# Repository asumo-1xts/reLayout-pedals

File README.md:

# reLayout-pedals

非営利な目的のもと、既存のエフェクターの基板レイアウトを引きなおします。

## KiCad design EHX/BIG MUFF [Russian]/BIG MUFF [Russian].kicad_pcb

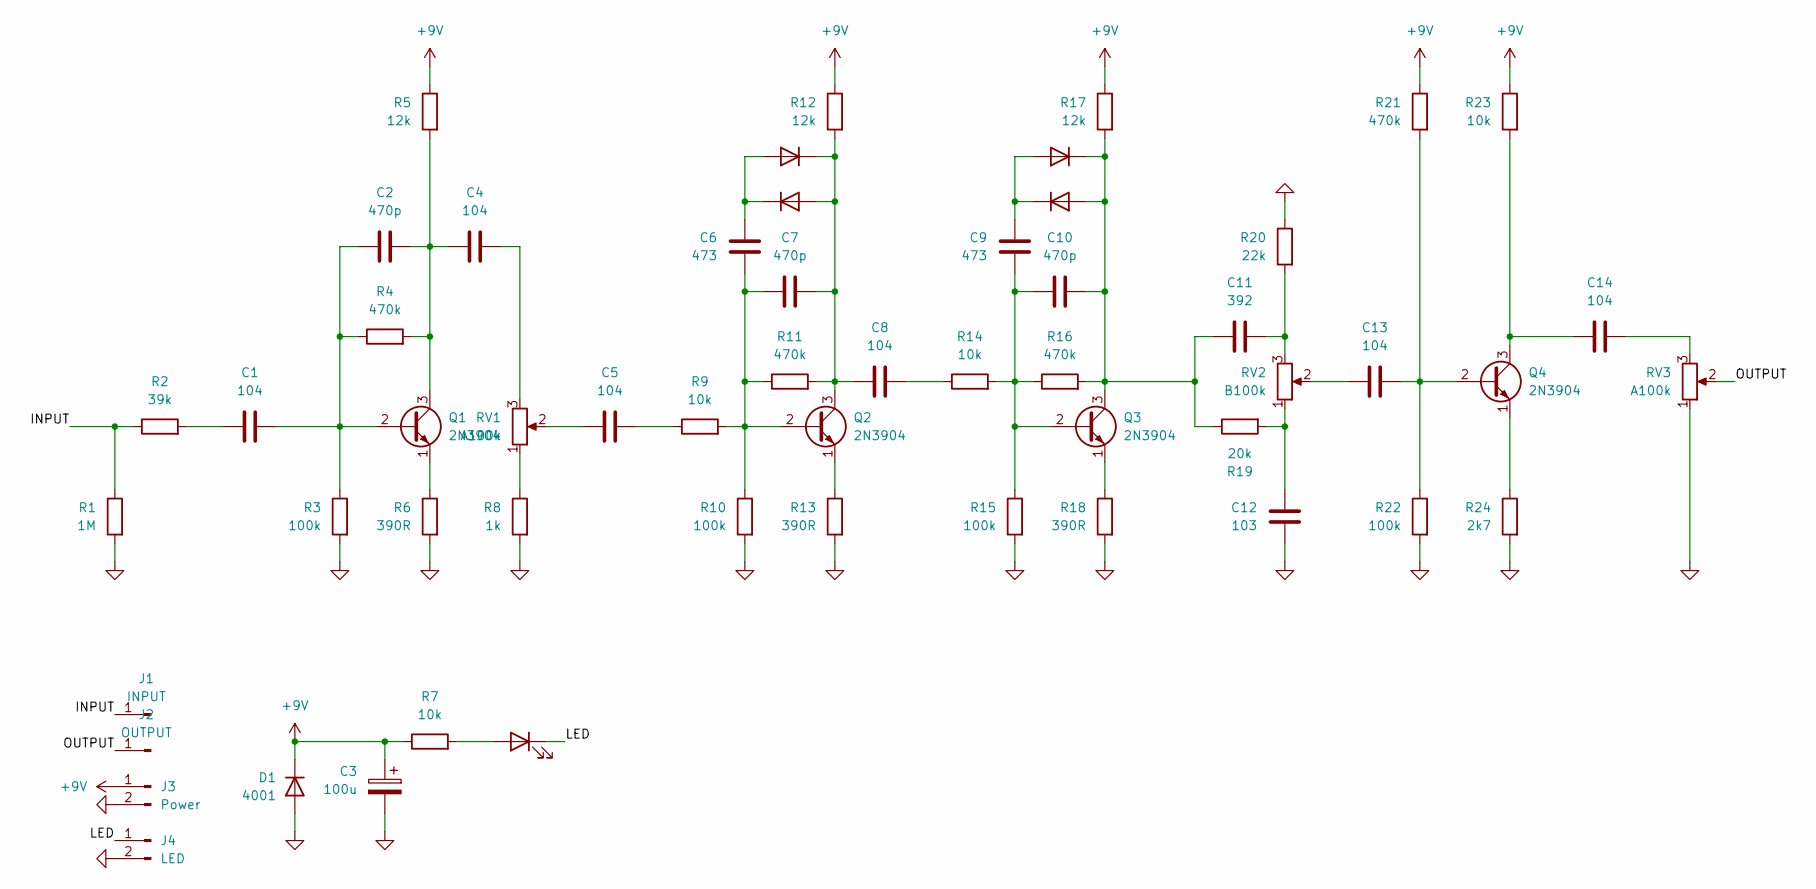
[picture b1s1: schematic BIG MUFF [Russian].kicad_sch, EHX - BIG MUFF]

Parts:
C1, C4, C5, C8, C13, C14: 104; C_Rect_L10.3mm_W5.7mm_P7.50mm_MKS4
C2, C7, C10: 470p; C_Rect_L7.2mm_W3.0mm_P5.00mm_FKS2_FKP2_MKS2_MKP2
C3: 100u; CP_Radial_D8.0mm_P3.50mm
C6, C9: 473; C_Rect_L7.2mm_W3.0mm_P5.00mm_FKS2_FKP2_MKS2_MKP2
C11: 392; C_Rect_L7.2mm_W3.0mm_P5.00mm_FKS2_FKP2_MKS2_MKP2
C12: 103; C_Rect_L7.2mm_W3.0mm_P5.00mm_FKS2_FKP2_MKS2_MKP2
D1: 4001; D_DO-41_SOD81_P7.62mm_Horizontal
D2: LED; LED_D5.0mm
D7, D8, D9, D10: 1N4148; D_DO-35_SOD27_P5.08mm_Vertical_AnodeUp
J1: INPUT; PinHeader_1x01_P2.54mm_Vertical
J2: OUTPUT; PinHeader_1x01_P2.54mm_Vertical
J3: Power; PinHeader_1x02_P2.54mm_Vertical
J4: LED; PinHeader_1x02_P2.54mm_Vertical
Q1, Q2, Q3, Q4: 2N3904; TO-92_Inline_Wide
R1: 1M; R_Axial_DIN0207_L6.3mm_D2.5mm_P7.62mm_Horizontal
R2: 39k; R_Axial_DIN0207_L6.3mm_D2.5mm_P7.62mm_Horizontal
R3, R10, R15, R22: 100k; R_Axial_DIN0207_L6.3mm_D2.5mm_P7.62mm_Horizontal
R4, R11, R16, R21: 470k; R_Axial_DIN0207_L6.3mm_D2.5mm_P7.62mm_Horizontal
R5, R12, R17: 12k; R_Axial_DIN0207_L6.3mm_D2.5mm_P7.62mm_Horizontal
R6, R13, R18: 390R; R_Axial_DIN0207_L6.3mm_D2.5mm_P7.62mm_Horizontal
R7, R9, R14, R23: 10k; R_Axial_DIN0207_L6.3mm_D2.5mm_P7.62mm_Horizontal
R8: 1k; R_Axial_DIN0207_L6.3mm_D2.5mm_P7.62mm_Horizontal
R19: 20k; R_Axial_DIN0207_L6.3mm_D2.5mm_P7.62mm_Horizontal
R20: 22k; R_Axial_DIN0207_L6.3mm_D2.5mm_P7.62mm_Horizontal
R24: 2k7; R_Axial_DIN0207_L6.3mm_D2.5mm_P7.62mm_Horizontal
RV1, RV3: A100k; Potentiometer_Omeg_PC16BU_Vertical
RV2: B100k; Potentiometer_Omeg_PC16BU_Vertical

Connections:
+9V: C3.1, D1.1 (K), J3.1, R5.1, R7.1, R12.1, R17.1, R21.1, R23.1
/INPUT: J1.1 (Pin_1_1), R1.1, R2.1
/LED: D2.1 (K), J4.1
/OUTPUT: J2.1 (Pin_1_1), RV3.2
GND: C3.2, C12.2, D1.2 (A), J3.2, J4.2, R1.2, R3.2, R6.2, R8.2, R10.2, R13.2, R15.2, R18.2, R20.1, R22.2, R24.2, RV3.1
unnamed: C1.1, R2.2
unnamed: C4.2, RV1.3
unnamed: C5.1, RV1.2
unnamed: C5.2, R9.1
unnamed: C8.2, R14.1
unnamed: C11.2, R20.2, RV2.3
unnamed: C12.1, R19.2, RV2.1
unnamed: C13.1, RV2.2
unnamed: C14.2, RV3.3
unnamed: D2.2 (A), R7.2
unnamed: C7.2, C8.1, D7.2 (A), D8.1 (K), Q2.3 (C), R11.2, R12.2
unnamed: C6.1, D7.1 (K), D8.2 (A)
unnamed: C9.1, D9.1 (K), D10.2 (A)
unnamed: C10.2, C11.1, D9.2 (A), D10.1 (K), Q3.3 (C), R16.2, R17.2, R19.1
unnamed: C1.2, C2.1, Q1.2 (B), R3.1, R4.1
unnamed: C2.2, C4.1, Q1.3 (C), R4.2, R5.2
unnamed: Q1.1 (E), R6.1
unnamed: C6.2, C7.1, Q2.2 (B), R9.2, R10.1, R11.1
unnamed: Q2.1 (E), R13.1
unnamed: C9.2, C10.1, Q3.2 (B), R14.2, R15.1, R16.1
unnamed: Q3.1 (E), R18.1
unnamed: C13.2, Q4.2 (B), R21.2, R22.1
unnamed: C14.1, Q4.3 (C), R23.2
unnamed: Q4.1 (E), R24.1
unnamed: R8.1, RV1.1

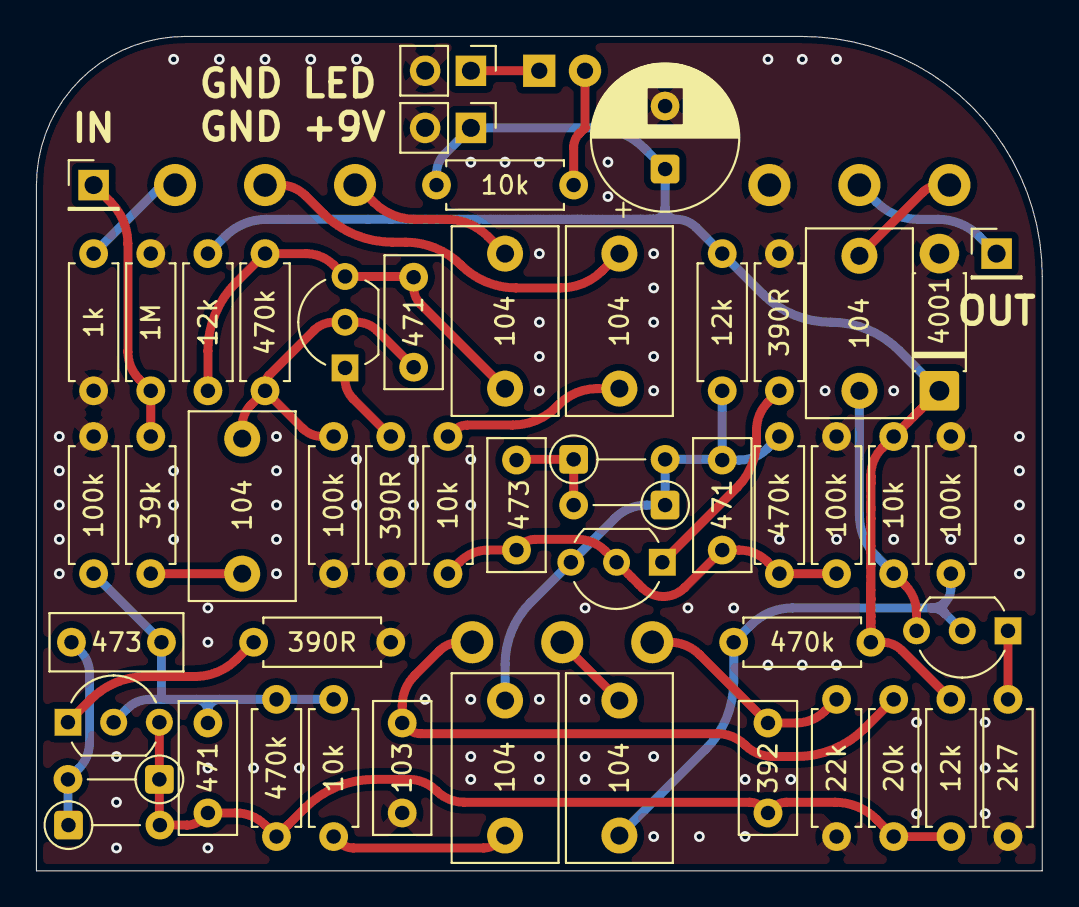
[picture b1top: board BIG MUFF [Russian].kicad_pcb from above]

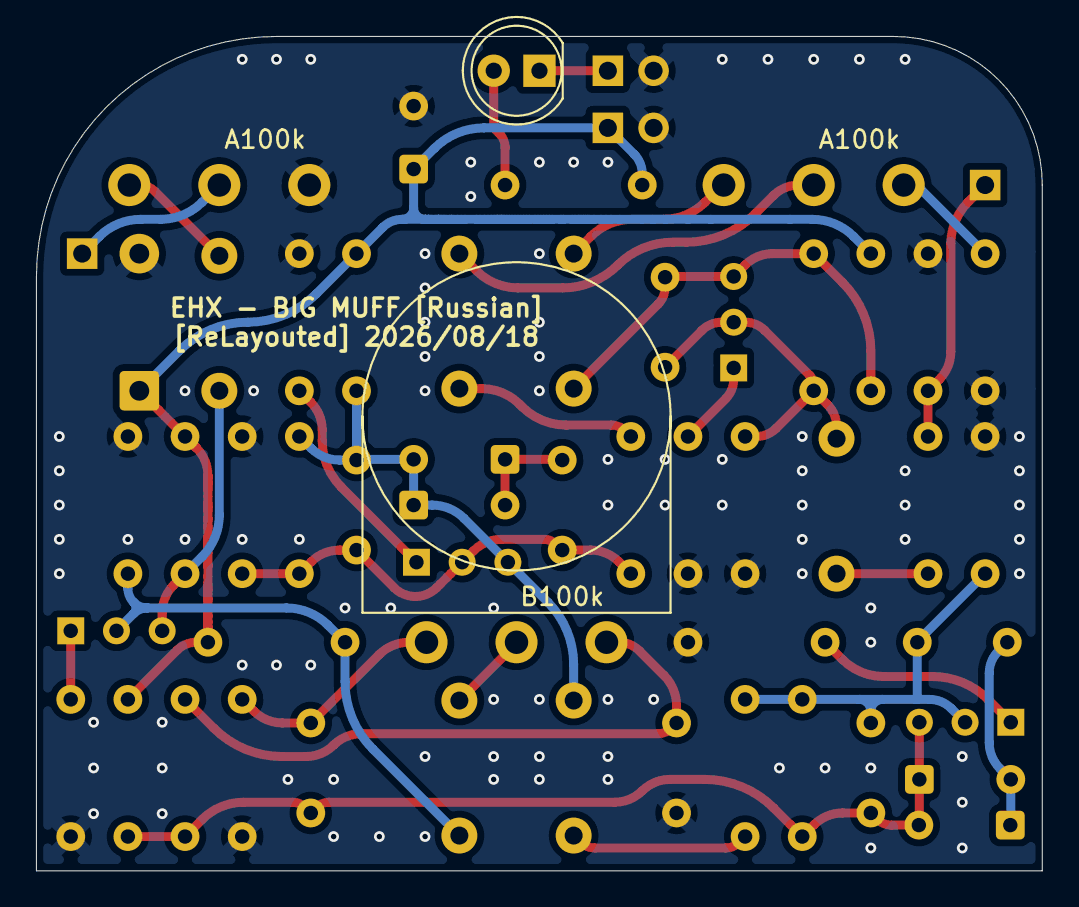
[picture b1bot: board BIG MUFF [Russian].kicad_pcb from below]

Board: 2 copper layers, 55.9 x 46.4 mm, 55 parts (4 on the bottom side), 30 nets.

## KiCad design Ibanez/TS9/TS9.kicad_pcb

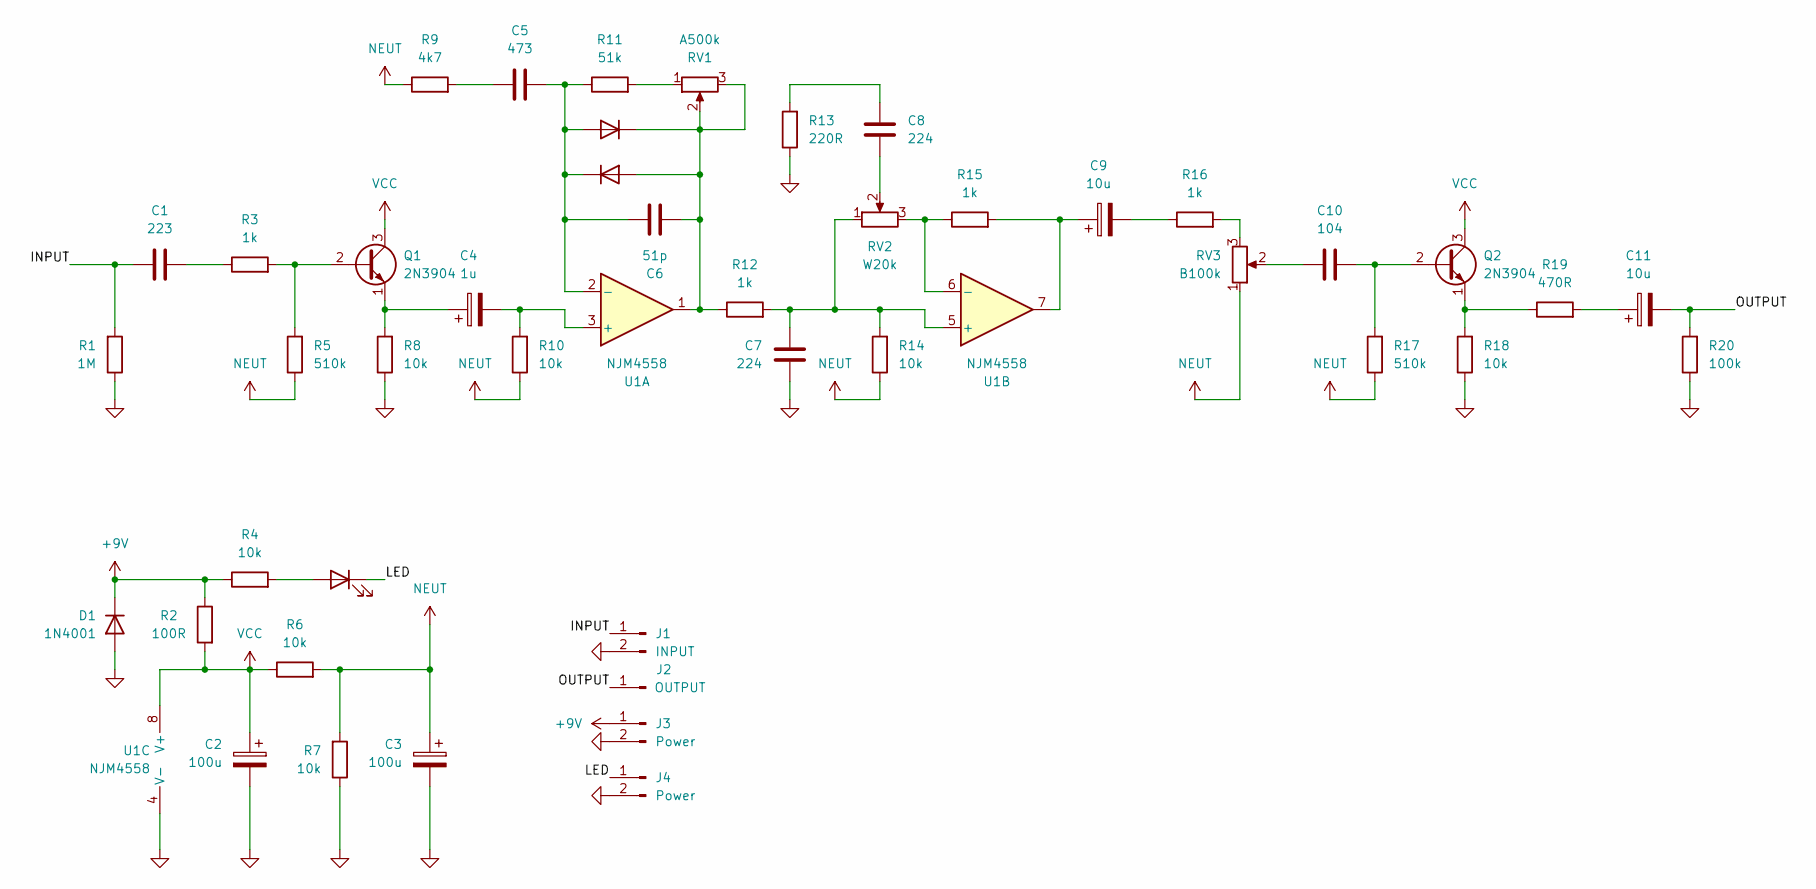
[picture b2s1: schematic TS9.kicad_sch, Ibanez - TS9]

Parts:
C1: 223; C_Rect_L7.2mm_W3.0mm_P5.00mm_FKS2_FKP2_MKS2_MKP2
C2, C3: 100u; CP_Radial_D8.0mm_P3.50mm
C4: 1u; CP_Radial_D5.0mm_P2.00mm
C5: 473; C_Rect_L7.2mm_W3.0mm_P5.00mm_FKS2_FKP2_MKS2_MKP2
C6: 51p; C_Disc_D3.8mm_W2.6mm_P2.50mm
C7, C8: 224; C_Rect_L10.3mm_W5.7mm_P7.50mm_MKS4
C9, C11: 10u; CP_Radial_D5.0mm_P2.00mm
C10: 104; C_Rect_L10.3mm_W5.7mm_P7.50mm_MKS4
D1: 1N4001; D_DO-41_SOD81_P7.62mm_Horizontal
D2: LED; LED_D5.0mm
D3, D4: 1N4148; D_DO-35_SOD27_P5.08mm_Vertical_AnodeUp
J1: INPUT; PinHeader_1x02_P2.54mm_Vertical
J2: OUTPUT; PinHeader_1x01_P2.54mm_Vertical
J3, J4: Power; PinHeader_1x02_P2.54mm_Vertical
Q1, Q2: 2N3904; TO-92_Inline_Wide
R1: 1M; R_Axial_DIN0207_L6.3mm_D2.5mm_P7.62mm_Horizontal
R2: 100R; R_Axial_DIN0207_L6.3mm_D2.5mm_P7.62mm_Horizontal
R3, R12, R15, R16: 1k; R_Axial_DIN0207_L6.3mm_D2.5mm_P7.62mm_Horizontal
R4, R6, R7, R8, R10, R14, R18: 10k; R_Axial_DIN0207_L6.3mm_D2.5mm_P7.62mm_Horizontal
R5, R17: 510k; R_Axial_DIN0207_L6.3mm_D2.5mm_P7.62mm_Horizontal
R9: 4k7; R_Axial_DIN0207_L6.3mm_D2.5mm_P7.62mm_Horizontal
R11: 51k; R_Axial_DIN0207_L6.3mm_D2.5mm_P7.62mm_Horizontal
R13: 220R; R_Axial_DIN0207_L6.3mm_D2.5mm_P7.62mm_Horizontal
R19: 470R; R_Axial_DIN0207_L6.3mm_D2.5mm_P7.62mm_Horizontal
R20: 100k; R_Axial_DIN0207_L6.3mm_D2.5mm_P7.62mm_Horizontal
RV1: A500k; Potentiometer_Omeg_PC16BU_Vertical
RV2: W20k; Potentiometer_Omeg_PC16BU_Vertical
RV3: B100k; Potentiometer_Omeg_PC16BU_Vertical
U1: NJM4558; DIP-8_W7.62mm

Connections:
+9V: D1.1 (K), J3.1, R2.1, R4.1
/INPUT: C1.2, J1.1, R1.2
/LED: D2.1 (K), J4.1
/OUTPUT: C11.2, J2.1 (Pin_1_1), R20.2
GND: C2.2, C3.2, C7.2, D1.2 (A), J1.2, J3.2, J4.2, R1.1, R7.1, R8.1, R13.1, R18.1, R20.1, U1.4 (V-)
NEUT: C3.1, R5.1, R6.2, R7.2, R9.1, R10.1, R14.1, R17.1, RV3.1
unnamed: C1.1, R3.1
unnamed: C5.2, R9.2
unnamed: C8.1, R13.2
unnamed: C8.2, RV2.2
unnamed: C9.1, R15.2, U1.7
unnamed: C9.2, R16.1
unnamed: C10.2, RV3.2
unnamed: C11.1, R19.2
unnamed: D2.2 (A), R4.2
unnamed: C5.1, C6.2, D3.2 (A), D4.1 (K), R11.1, U1.2 (-)
unnamed: C6.1, D3.1 (K), D4.2 (A), R12.1, RV1.2, RV1.3, U1.1
unnamed: Q1.2 (B), R3.2, R5.2
unnamed: C4.1, Q1.1 (E), R8.2
unnamed: C10.1, Q2.2 (B), R17.2
unnamed: Q2.1 (E), R18.2, R19.1
unnamed: R11.2, RV1.1
unnamed: R16.2, RV3.3
unnamed: C4.2, R10.2, U1.3 (+)
unnamed: C7.1, R12.2, R14.2, RV2.1, U1.5 (+)
unnamed: R15.1, RV2.3, U1.6 (-)
VCC: C2.1, Q1.3 (C), Q2.3 (C), R2.2, R6.1, U1.8 (V+)

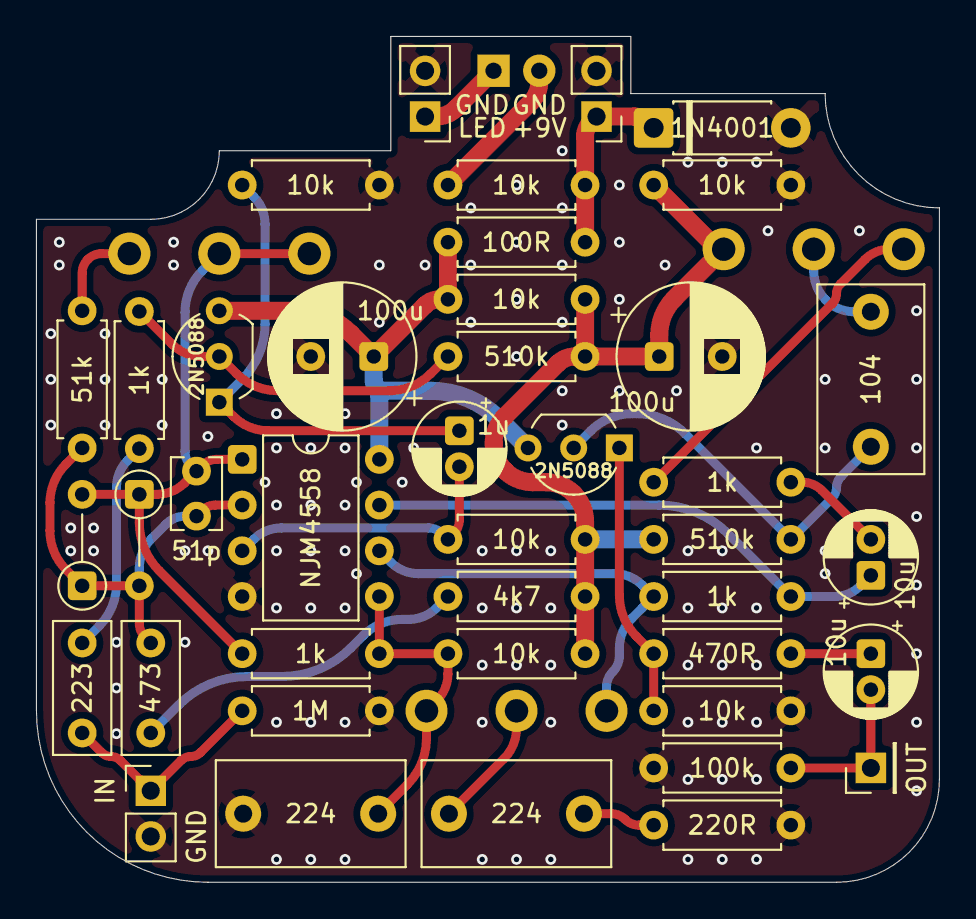
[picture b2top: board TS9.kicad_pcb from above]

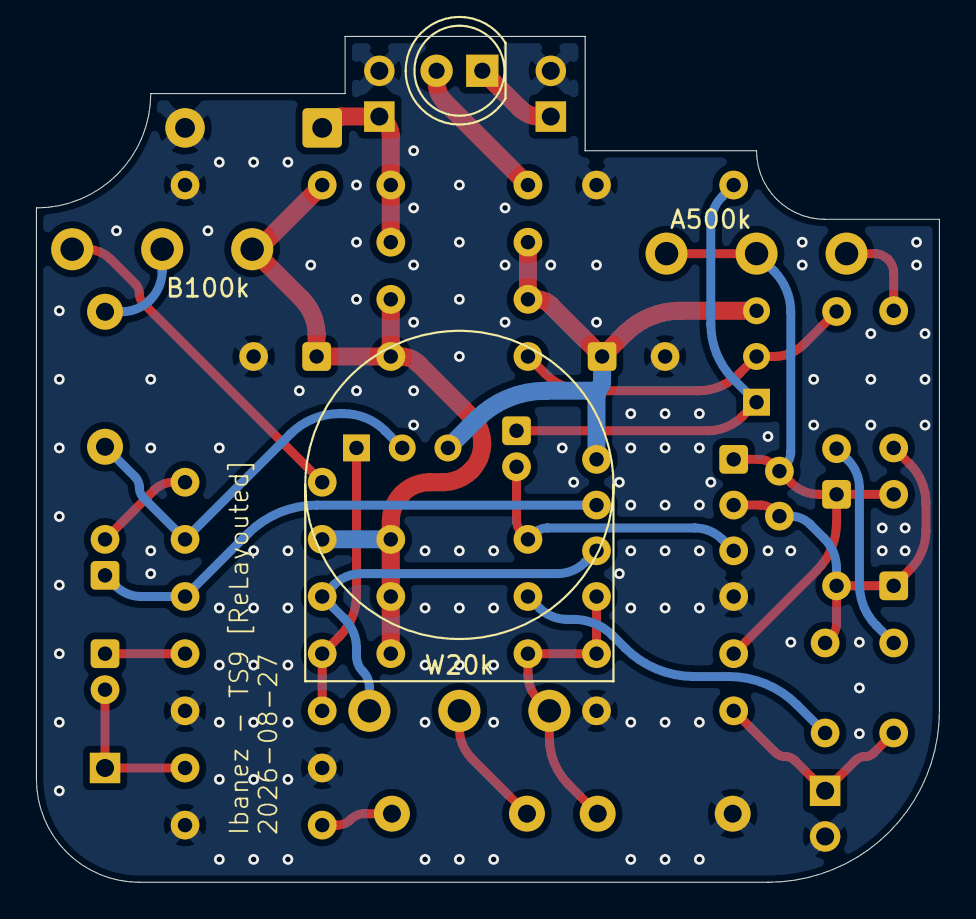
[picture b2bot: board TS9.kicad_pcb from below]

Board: 2 copper layers, 50.2 x 47.0 mm, 45 parts (4 on the bottom side), 27 nets.

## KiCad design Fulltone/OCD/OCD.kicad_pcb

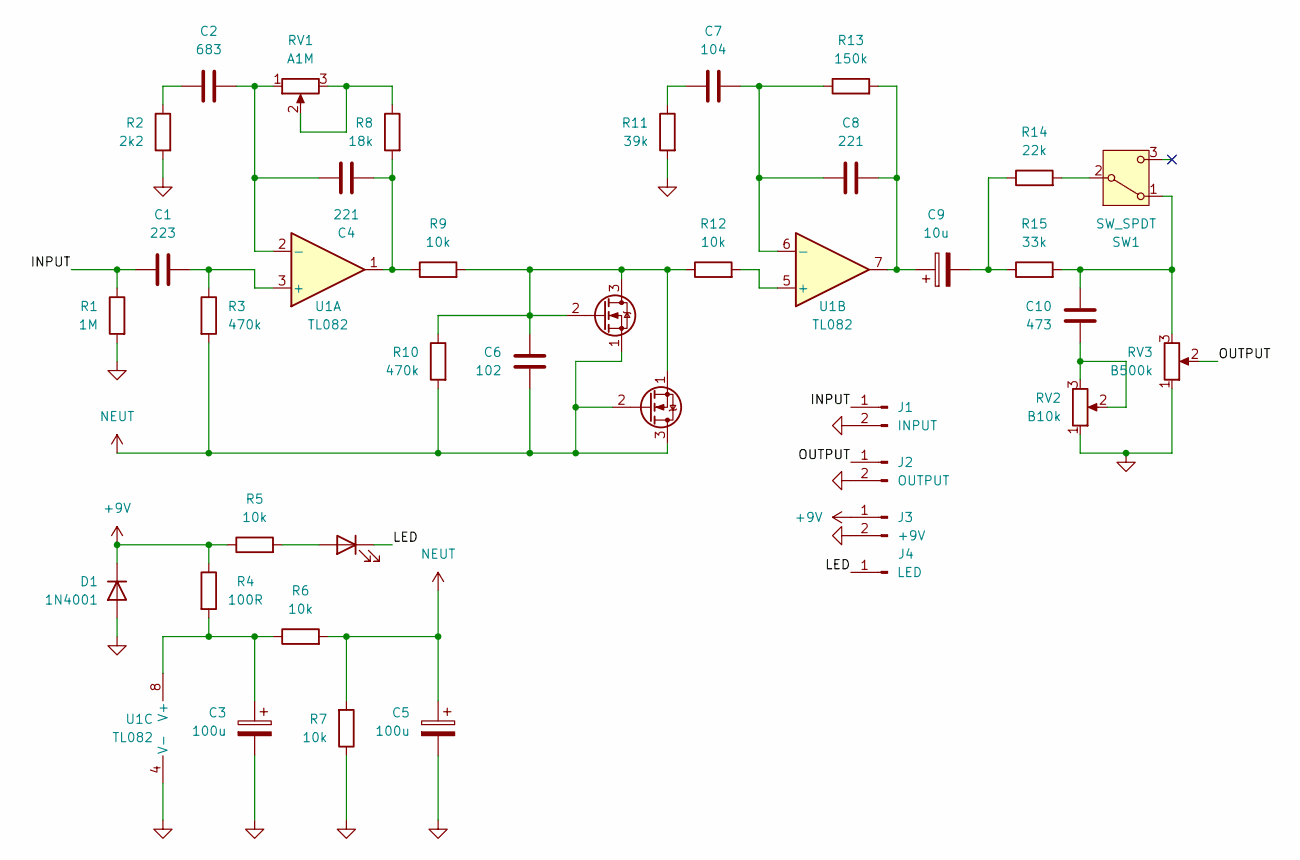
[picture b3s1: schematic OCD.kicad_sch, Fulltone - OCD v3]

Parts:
C1: 223; C_Rect_L7.2mm_W3.0mm_P5.00mm_FKS2_FKP2_MKS2_MKP2
C2: 683; C_Rect_L7.2mm_W4.5mm_P5.00mm_FKS2_FKP2_MKS2_MKP2
C3, C5: 100u; CP_Radial_D8.0mm_P3.50mm
C4, C8: 221; C_Rect_L7.2mm_W3.0mm_P5.00mm_FKS2_FKP2_MKS2_MKP2
C6: 102; C_Rect_L7.2mm_W3.0mm_P5.00mm_FKS2_FKP2_MKS2_MKP2
C7: 104; C_Rect_L10.3mm_W5.7mm_P7.50mm_MKS4
C9: 10u; CP_Radial_D5.0mm_P2.00mm
C10: 473; C_Rect_L7.2mm_W3.0mm_P5.00mm_FKS2_FKP2_MKS2_MKP2
D1: 1N4001; D_DO-41_SOD81_P7.62mm_Horizontal
D2: LED; LED_D5.0mm
J1: INPUT; PinHeader_1x02_P2.54mm_Vertical
J2: OUTPUT; PinHeader_1x02_P2.54mm_Vertical
J3: +9V; PinHeader_1x02_P2.54mm_Vertical
J4: LED; PinHeader_1x01_P2.54mm_Vertical
Q1, Q2: 2N7000; TO-92_Inline_Wide
R1: 1M; R_Axial_DIN0207_L6.3mm_D2.5mm_P7.62mm_Horizontal
R2: 2k2; R_Axial_DIN0207_L6.3mm_D2.5mm_P7.62mm_Horizontal
R3, R10: 470k; R_Axial_DIN0207_L6.3mm_D2.5mm_P7.62mm_Horizontal
R4: 100R; R_Axial_DIN0207_L6.3mm_D2.5mm_P7.62mm_Horizontal
R5, R6, R7, R9, R12: 10k; R_Axial_DIN0207_L6.3mm_D2.5mm_P7.62mm_Horizontal
R8: 18k; R_Axial_DIN0207_L6.3mm_D2.5mm_P7.62mm_Horizontal
R11: 39k; R_Axial_DIN0207_L6.3mm_D2.5mm_P7.62mm_Horizontal
R13: 150k; R_Axial_DIN0207_L6.3mm_D2.5mm_P7.62mm_Horizontal
R14: 22k; R_Axial_DIN0207_L6.3mm_D2.5mm_P7.62mm_Horizontal
R15: 33k; R_Axial_DIN0207_L6.3mm_D2.5mm_P7.62mm_Horizontal
RV1: A1M; Potentiometer_Omeg_PC16BU_Vertical
RV2: B10k; Potentiometer_Omeg_PC16BU_Vertical
RV3: B500k; Potentiometer_Omeg_PC16BU_Vertical
SW1: SW_SPDT; PinHeader_1x03_P2.54mm_Vertical
U1: TL082; DIP-8_W7.62mm

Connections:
+9V: D1.1 (K), J3.1, R4.1, R5.1
/INPUT: C1.1, J1.1, R1.1
/LED: D2.1 (K), J4.1 (Pin_1_1)
/OUTPUT: J2.1, RV3.2
GND: C3.2, C5.2, D1.2 (A), J1.2, J2.2, J3.2, R1.2, R2.2, R7.1, R11.2, RV2.1, RV3.1, U1.4 (V-)
NEUT: C5.1, C6.2, Q1.1 (S), Q2.2 (G), Q2.3 (D), R3.2, R6.2, R7.2, R10.2
unnamed: C2.1, R2.1
unnamed: C4.2, R8.2, R9.1, U1.1
unnamed: C7.1, R11.1
unnamed: C8.2, C9.1, R13.2, U1.7
unnamed: C9.2, R14.1, R15.1
unnamed: C10.2, RV2.2, RV2.3
unnamed: D2.2 (A), R5.2
unnamed: C6.1, Q1.2 (G), Q1.3 (D), Q2.1 (S), R9.2, R10.1, R12.1
unnamed: R8.1, RV1.2, RV1.3
unnamed: C10.1, R15.2, RV3.3, SW1.1 (A)
unnamed: R14.2, SW1.2 (B)
unnamed: C1.2, R3.1, U1.3 (+)
unnamed: C2.2, C4.1, RV1.1, U1.2 (-)
unnamed: R12.2, U1.5 (+)
unnamed: C7.2, C8.1, R13.1, U1.6 (-)
unnamed: C3.1, R4.2, R6.1, U1.8 (V+)

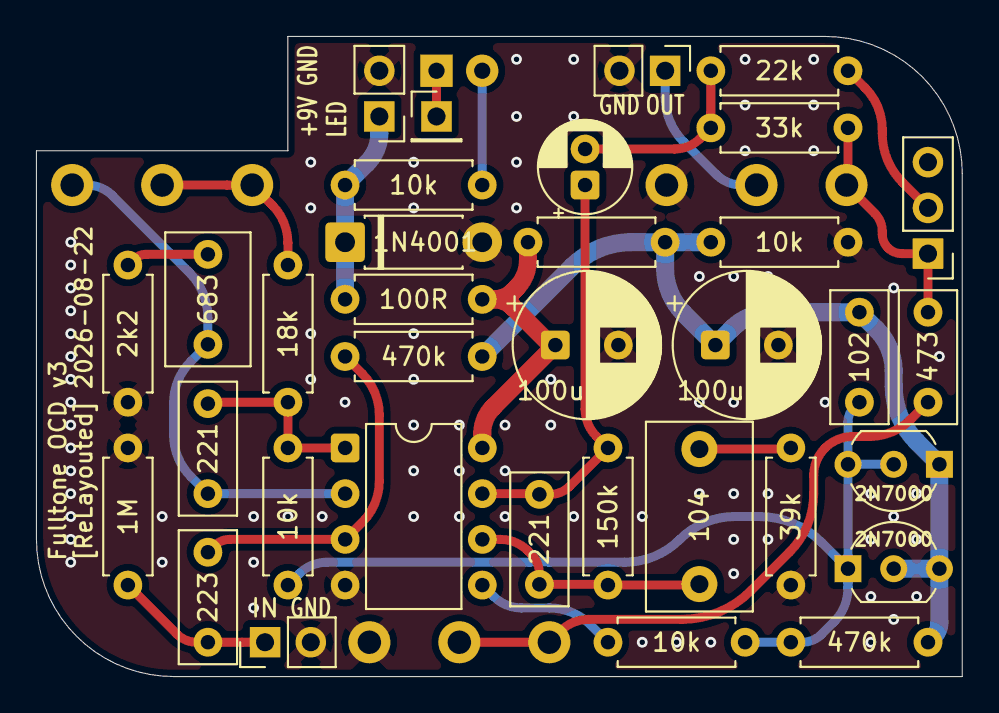
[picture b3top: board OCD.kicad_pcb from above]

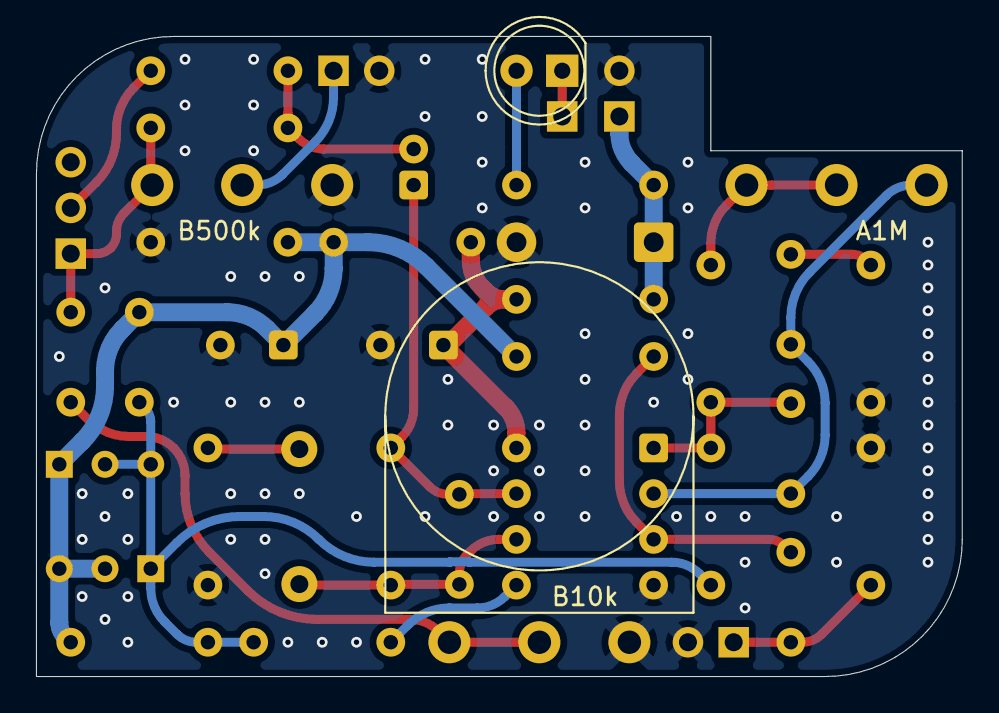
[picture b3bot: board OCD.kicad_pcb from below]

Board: 2 copper layers, 51.4 x 35.6 mm, 38 parts (4 on the bottom side), 22 nets.

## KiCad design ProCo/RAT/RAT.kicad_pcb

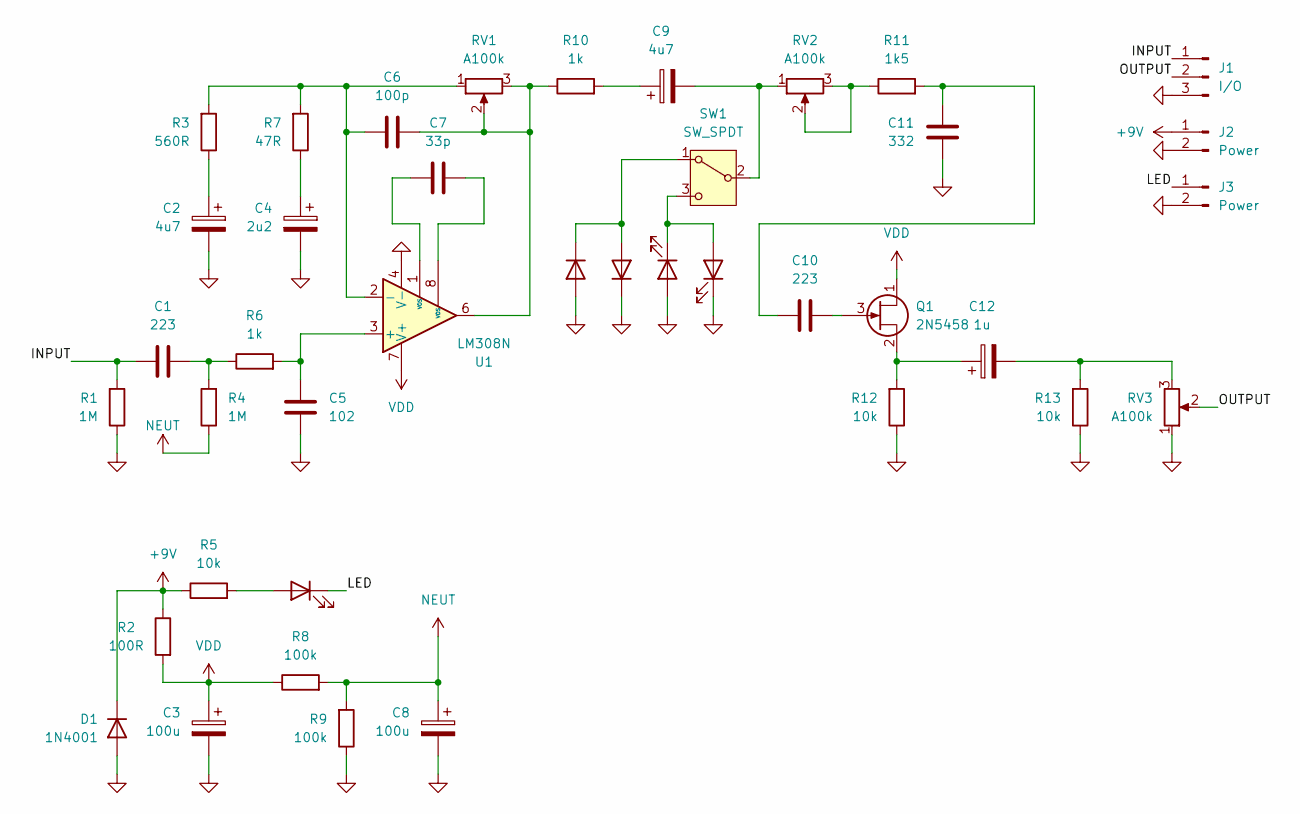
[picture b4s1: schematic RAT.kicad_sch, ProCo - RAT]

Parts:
C1, C10: 223; C_Rect_L7.2mm_W3.0mm_P5.00mm_FKS2_FKP2_MKS2_MKP2
C2, C9: 4u7; CP_Radial_D5.0mm_P2.00mm
C3, C8: 100u; CP_Radial_D8.0mm_P3.50mm
C4: 2u2; CP_Radial_D5.0mm_P2.00mm
C5: 102; C_Rect_L7.2mm_W3.0mm_P5.00mm_FKS2_FKP2_MKS2_MKP2
C6: 100p; C_Disc_D3.8mm_W2.6mm_P2.50mm
C7: 33p; C_Disc_D3.8mm_W2.6mm_P2.50mm
C11: 332; C_Rect_L7.2mm_W3.0mm_P5.00mm_FKS2_FKP2_MKS2_MKP2
C12: 1u; CP_Radial_D5.0mm_P2.00mm
D1: 1N4001; D_DO-41_SOD81_P7.62mm_Horizontal
D2, D5, D6: LED; LED_D5.0mm
D3, D4: 1N4148; D_DO-35_SOD27_P5.08mm_Vertical_AnodeUp
J1: I/O; PinHeader_1x03_P2.54mm_Vertical
J2, J3: Power; PinHeader_1x02_P2.54mm_Vertical
Q1: 2N5458; TO-92_Inline_Wide
R1, R4: 1M; R_Axial_DIN0207_L6.3mm_D2.5mm_P7.62mm_Horizontal
R2: 100R; R_Axial_DIN0207_L6.3mm_D2.5mm_P7.62mm_Horizontal
R3: 560R; R_Axial_DIN0207_L6.3mm_D2.5mm_P7.62mm_Horizontal
R5, R12, R13: 10k; R_Axial_DIN0207_L6.3mm_D2.5mm_P7.62mm_Horizontal
R6, R10: 1k; R_Axial_DIN0207_L6.3mm_D2.5mm_P7.62mm_Horizontal
R7: 47R; R_Axial_DIN0207_L6.3mm_D2.5mm_P7.62mm_Horizontal
R8, R9: 100k; R_Axial_DIN0207_L6.3mm_D2.5mm_P7.62mm_Horizontal
R11: 1k5; R_Axial_DIN0207_L6.3mm_D2.5mm_P7.62mm_Horizontal
RV1, RV2, RV3: A100k; Potentiometer_Omeg_PC16BU_Vertical
SW1: SW_SPDT; PinHeader_1x03_P2.54mm_Vertical
U1: LM308N; DIP-8_W7.62mm

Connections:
+9V: D1.1 (K), J2.1, R2.1, R5.1
/INPUT: C1.1, J1.1, R1.2
/LED: D2.1 (K), J3.1
/OUTPUT: J1.2, RV3.2
GND: C2.2, C3.2, C4.2, C5.2, C8.2, C11.2, D1.2 (A), D3.2 (A), D4.1 (K), D5.2 (A), D6.1 (K), J1.3, J2.2, J3.2, R1.1, R9.1, R12.1, R13.1, RV3.1, U1.4 (V-)
NEUT: C8.1, R4.1, R8.2, R9.2
unnamed: C1.2, R4.2, R6.1
unnamed: C2.1, R3.1
unnamed: C4.1, R7.1
unnamed: C6.2, R10.1, RV1.2, RV1.3, U1.6
unnamed: C7.1, U1.1 (VOS)
unnamed: C7.2, U1.8 (VOS)
unnamed: C9.1, R10.2
unnamed: C10.1, C11.1, R11.2
unnamed: C12.2, R13.2, RV3.3
unnamed: D2.2 (A), R5.2
unnamed: D3.1 (K), D4.2 (A), SW1.1 (A)
unnamed: D5.1 (K), D6.2 (A), SW1.3 (C)
unnamed: C10.2, Q1.3 (G)
unnamed: C12.1, Q1.2 (S), R12.2
unnamed: R11.1, RV2.2, RV2.3
unnamed: C9.2, RV2.1, SW1.2 (B)
unnamed: C5.1, R6.2, U1.3 (+)
unnamed: C6.1, R3.2, R7.2, RV1.1, U1.2 (-)
VDD: C3.1, Q1.1 (D), R2.2, R8.1, U1.7 (V+)

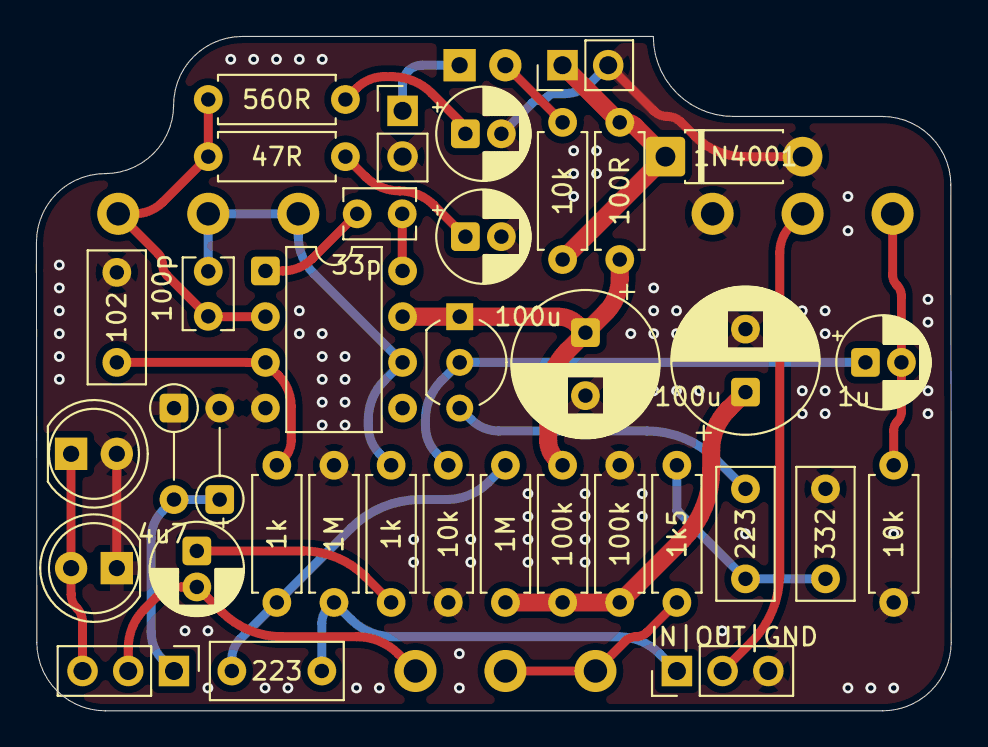
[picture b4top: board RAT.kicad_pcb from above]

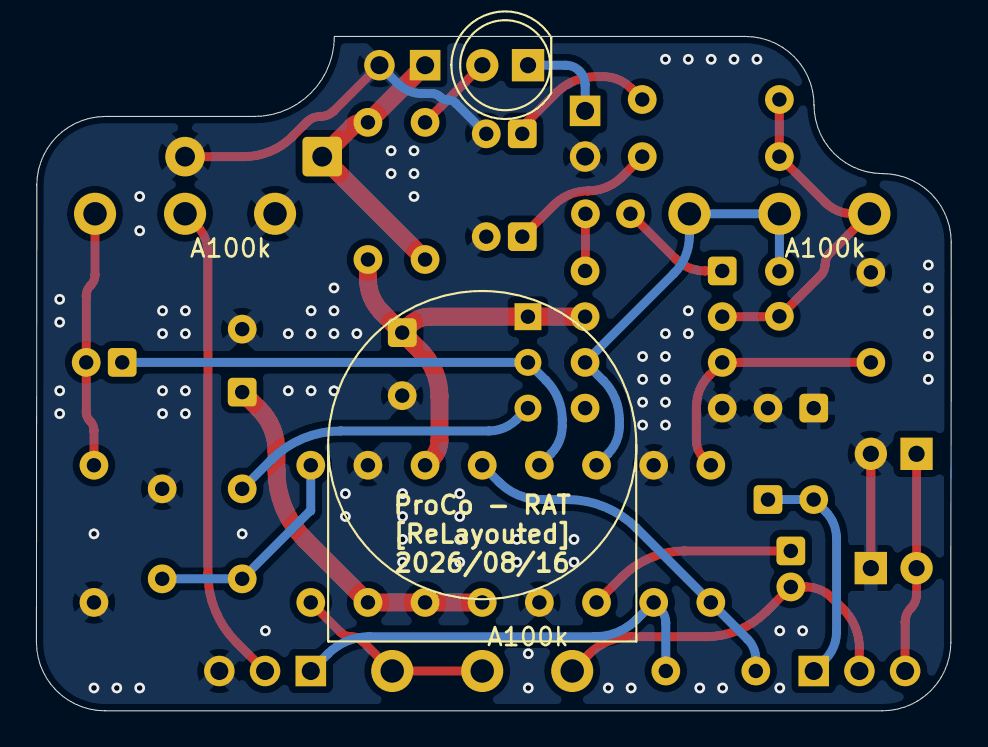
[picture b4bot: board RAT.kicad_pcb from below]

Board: 2 copper layers, 50.8 x 37.5 mm, 40 parts (4 on the bottom side), 25 nets.

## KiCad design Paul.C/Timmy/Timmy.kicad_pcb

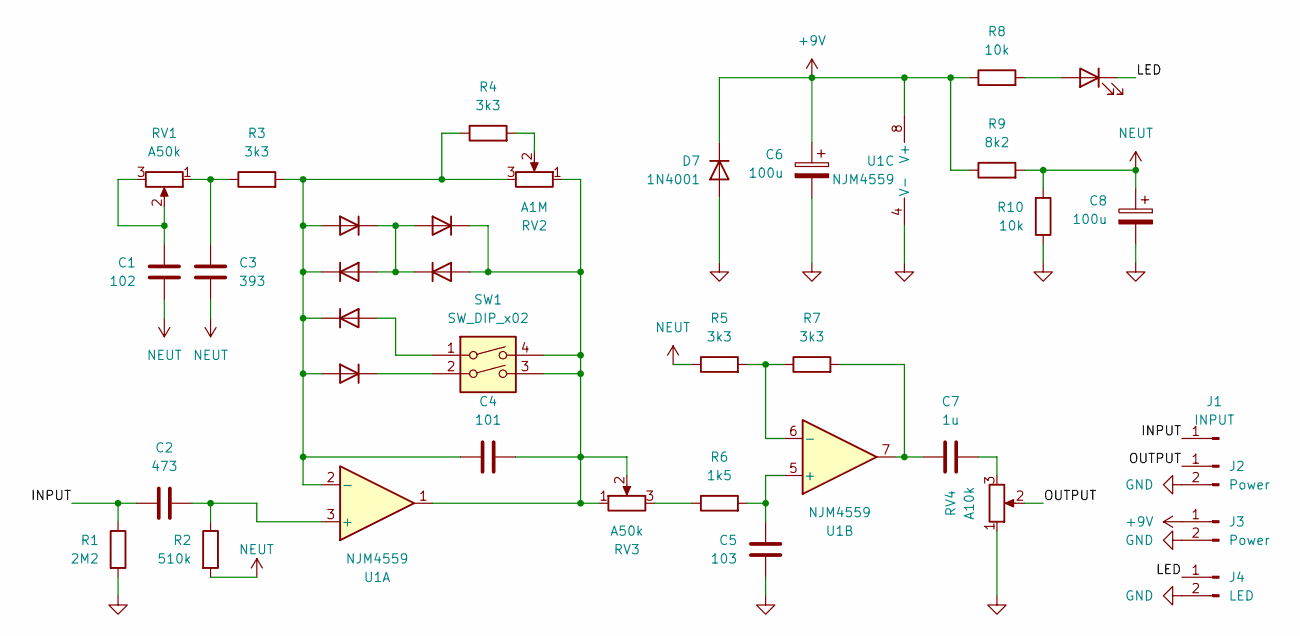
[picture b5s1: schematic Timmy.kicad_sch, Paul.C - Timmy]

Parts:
C1: 102; C_Rect_L7.2mm_W3.0mm_P5.00mm_FKS2_FKP2_MKS2_MKP2
C2: 473; C_Rect_L7.2mm_W3.0mm_P5.00mm_FKS2_FKP2_MKS2_MKP2
C3: 393; C_Rect_L7.2mm_W3.0mm_P5.00mm_FKS2_FKP2_MKS2_MKP2
C4: 101; C_Disc_D3.8mm_W2.6mm_P2.50mm
C5: 103; C_Rect_L7.2mm_W3.0mm_P5.00mm_FKS2_FKP2_MKS2_MKP2
C6, C8: 100u; CP_Radial_D8.0mm_P3.50mm
C7: 1u; C_Rect_L7.0mm_W6.5mm_P5.00mm
D1, D2, D3, D4, D5, D6: 1N4148; D_DO-35_SOD27_P5.08mm_Vertical_AnodeUp
D7: 1N4001; D_DO-41_SOD81_P7.62mm_Horizontal
D8: LED; LED_D5.0mm
J1: INPUT; PinHeader_1x01_P2.54mm_Vertical
J2, J3: Power; PinHeader_1x02_P2.54mm_Vertical
J4: LED; PinHeader_1x02_P2.54mm_Vertical
R1: 2M2; R_Axial_DIN0207_L6.3mm_D2.5mm_P7.62mm_Horizontal
R2: 510k; R_Axial_DIN0207_L6.3mm_D2.5mm_P7.62mm_Horizontal
R3, R4, R5, R7: 3k3; R_Axial_DIN0207_L6.3mm_D2.5mm_P7.62mm_Horizontal
R6: 1k5; R_Axial_DIN0207_L6.3mm_D2.5mm_P7.62mm_Horizontal
R8, R10: 10k; R_Axial_DIN0207_L6.3mm_D2.5mm_P7.62mm_Horizontal
R9: 8k2; R_Axial_DIN0207_L6.3mm_D2.5mm_P7.62mm_Horizontal
RV1, RV3: A50k; Potentiometer_Omeg_PC16BU_Vertical
RV2: A1M; Potentiometer_Omeg_PC16BU_Vertical
RV4: A10k; Potentiometer_Omeg_PC16BU_Vertical
SW1: SW_DIP_x02; SW_DIP_SPSTx02_Slide_9.78x7.26mm_W7.62mm_P2.54mm
U1: NJM4559; DIP-8_W7.62mm

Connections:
+9V: C6.1, D7.1 (K), J3.1, R8.1, R9.1, U1.8 (V+)
/INPUT: C2.1, J1.1 (Pin_1_1), R1.1
/LED: D8.1 (K), J4.1
/OUTPUT: J2.1, RV4.2
GND: C5.2, C6.2, C8.2, D7.2 (A), J2.2, J3.2, J4.2, R1.2, R10.1, RV4.1, U1.4 (V-)
NEUT: C1.2, C3.2, C8.1, R2.2, R5.1, R9.2, R10.2
unnamed: C1.1, RV1.2, RV1.3
unnamed: C3.1, R3.1, RV1.1
unnamed: C7.1, R7.2, U1.7
unnamed: C7.2, RV4.3
unnamed: C4.1, D1.2 (A), D2.1 (K), D3.1 (K), D4.2 (A), R3.2, R4.1, RV2.3, U1.2 (-)
unnamed: D1.1 (K), D2.2 (A), D5.2 (A), D6.1 (K)
unnamed: D3.2 (A), SW1.1
unnamed: D4.1 (K), SW1.2
unnamed: C4.2, D5.1 (K), D6.2 (A), RV2.1, RV3.1, RV3.2, SW1.3, SW1.4, U1.1
unnamed: D8.2 (A), R8.2
unnamed: R4.2, RV2.2
unnamed: R6.1, RV3.3
unnamed: C2.2, R2.1, U1.3 (+)
unnamed: C5.1, R6.2, U1.5 (+)
unnamed: R5.2, R7.1, U1.6 (-)

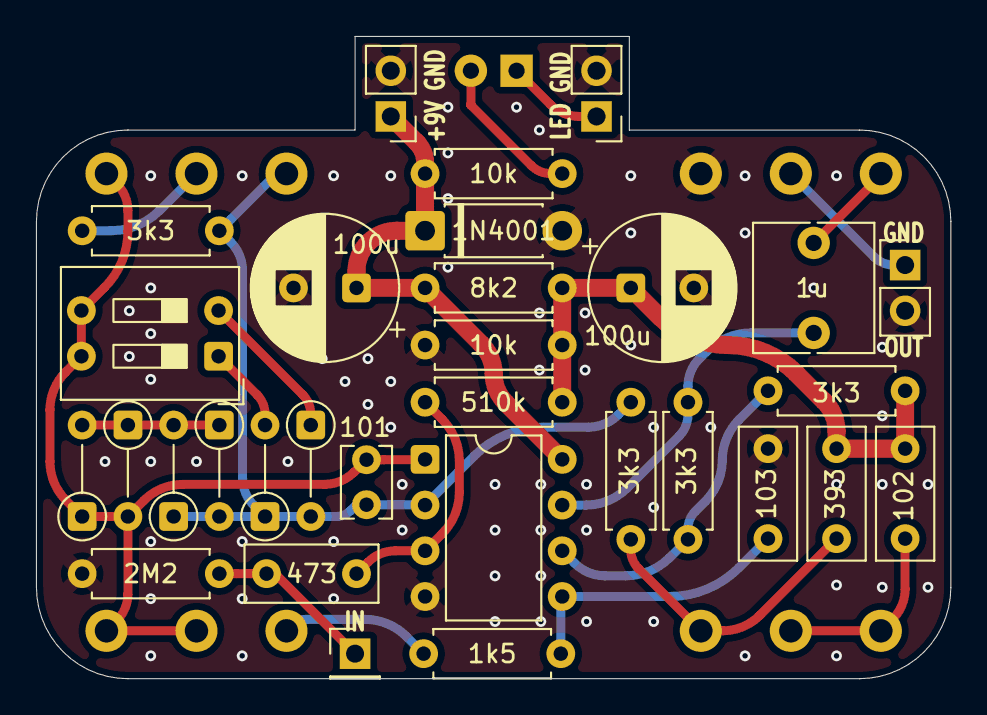
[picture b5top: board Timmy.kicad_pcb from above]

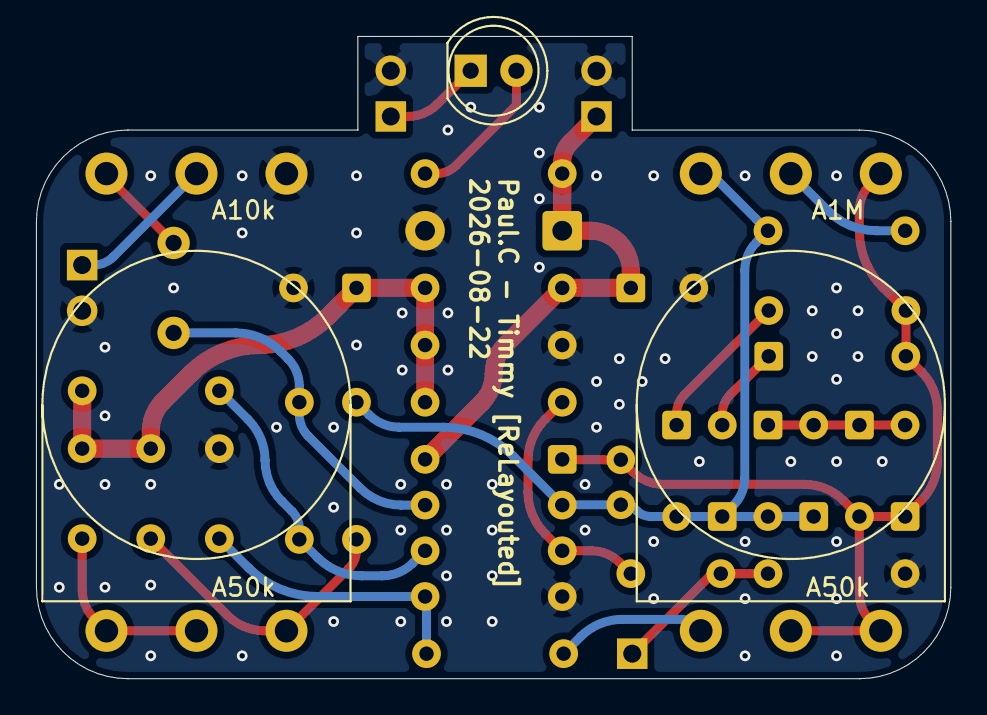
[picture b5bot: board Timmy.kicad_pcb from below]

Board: 2 copper layers, 50.8 x 35.7 mm, 36 parts (5 on the bottom side), 21 nets.
